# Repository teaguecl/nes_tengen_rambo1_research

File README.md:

# Tengen RAMBO-1 (337006, iNES mapper 64): reverse engineering

A measured description of the Tengen RAMBO-1 mapper chip. It was characterised on a jig (Arduino Mega, later an RP2350
adapter with a PIO engine at 150 MHz), with a logic analyser on a running console, and checked with test ROMs on a real NES.
Every claim in the documents carries an evidence marker.

**Audience:** Software emulator authors, FPGA and cartridge designers.

## Where to start

| If you want to | Read |
|---|---|
| Check a claim | [`docs/findings.md`](docs/findings.md): F-001 to F-090, each with the experiment behind it. This is the heart of the research and everything else is derived from it. |
| Write or fix a mapper 64 emulator | [`docs/emulator_guide.md`](docs/emulator_guide.md). Section 4A is for people who already have an MMC3. For hardware-verified test ROMs, see [`rom/README.md`](rom/README.md) |
| Pins, timing figures and an HDL starting point | [`docs/fpga_notes.md`](docs/fpga_notes.md) |
| Understand how it works | [`docs/functional_description.md`](docs/functional_description.md) |
| Rebuild it in an FPGA or design a cartridge | [`docs/fpga_notes.md`](docs/fpga_notes.md), [`docs/timing_measurements.md`](docs/timing_measurements.md) |
| See what differs from NESdev Wiki | [`docs/nesdev_verification.md`](docs/nesdev_verification.md) |

## What is in the repository

| Path | Contents |
|---|---|
| `docs/` | The documents above, pin maps (`j2_*.csv`), the cart netlist, the logic-analyser guide, the RP2350 adapter plan and bring-up notes |
| `reference/` | `rambo1.py`, a small executable model of the chip (about 200 lines, every rule commented with its finding number), and its unit tests (`test_rambo1.py`) |
| `rom/` | Six test ROMs (G1 to G6, 62 tests) in ca65 assembly. They print PASS or FAIL and run on a real NES. `rom/tools/hwsim.py` runs them on a software model of the chip, and `rom/tools/run_checks.sh` runs everything |
| `firmware/rambo_jig/` | Arduino Mega 2560 firmware for the first jig |
| `firmware/rp2350_jig/` | RP2350 adapter firmware (PIO engine) and the host tools for experiments E2 to E10 |
| `hardware/` | KiCad projects, gerbers and BOMs for the jig board and the two adapters, with a README and the netlist generator |
| `tools/`, `experiments/` | Analysis scripts and experiment definitions for the Mega jig and the logic-analyser captures |
| `captures/`, `results/` | The raw evidence: sigrok captures and CSV logs |
| `pin_check/` | The continuity check of the pinout |

## Headline results

- The chip decodes registers on CPU A0, A13 and A14 only. It has R8, R9 and RF, a 1 KB CHR mode (K), and a CPU-cycle IRQ mode that the MMC3 does not have.
- The power-on state is defined: /IRQ asserted, PRG banks `$1F`, CHR bank 0 in 1 KB mode, latch `$FF`, vertical mirroring, and the counter already running in CPU-cycle mode (F-088).
- The A12 filter needs 16 consecutive M2 falls with A12 low. It samples A12 at the M2 fall only (F-081, F-084).
- The write window closes at the first of the M2 fall, the /ROMSEL rise and the R/W rise, and the data is latched at that instant (F-082).
- CHR bank registers and `$A000` are transparent during the window. R6, R7 and RF are not (F-089).
- The IRQ enable flag is tested at the M2 fall (F-071, F-072, F-074, F-090).
- An A12 to CPU mode switch while the filter is not full expires 4 cycles early (F-087). Test ROM G4 test 13 confirms it on the console.

## The hardware

<table>
<tr>
<td align="center"><br><sub>The three boards: Arduino Mega with its adapter (left), RP2350 adapter (top right) and the RAMBO-1 jig / flash cart (bottom).</sub></td>
<td align="center"><br><sub>The RP2350 adapter connected to the jig board by the 40-way ribbon (J2).</sub></td>
</tr>
<tr>
<td align="center"><br><sub>The jig board with two flash chips, used as a flash cart in an NES: the test ROMs ran from here.</sub></td>
<td align="center"><br><sub>The same cart with the 8-channel logic analyser listening on the J2 header.</sub></td>
</tr>
</table>

## Status and limits

- Everything was measured on **one chip** in one NTSC console. Differences between chip revisions or PAL consoles are unknown.
- Unresolved: the origin of the power-on /IRQ (F-034), the open-drain release time (F-080), the CIC, and pin 19's purpose beyond what F-046 and F-047 show.
- All six test ROMs pass on the real cart (62 tests).

## Building and running

All commands run in a Docker container through `./drun.sh`.
The first call builds the image: cc65 2.19, Python 3, sigrok-cli, SKiDL, CMake, the Pico SDK 2.3.1 and the Arm toolchain.

`./drun.sh --device /dev/ttyACM0 ...` passes the RP2350 adapter's serial port through.

The image does not include KiCad or the Arduino IDE.
Without Docker, install the same tools yourself (see the `Dockerfile`) and drop the `./drun.sh`.

- **Test ROMs:** `./drun.sh "cd rom && make"`

The ready-made images are in `rom/build/` (the six `g*.nes` files).
  Expected MD5 of the six test ROMs (`rom/build/g*.nes`, 524,304 bytes each):

  | Image | Tests | MD5 |
  |---|---|---|
  | `g1_power_on.nes` | Power-on state (after a power cycle only) | `1a89a4dbddda0af36ee58ceca1df30f4` |
  | `g2_banking.nes` | PRG/CHR banking, K/P/C bits, R8/R9, mirroring | `760dfb3409ce149c3a1709a5ff7fed32` |
  | `g3_bus.nes` | Register decode, /CE, bus conflicts, reads | `fb8c870fffdd3aa76c1b4d2a9c10f47f` |
  | `g4_cpu_irq.nes` | CPU-cycle IRQ mode and its timing races | `789a5981e2c5eeb491ff50dc27364bac` |
  | `g5_a12_irq.nes` | A12 (scanline) IRQ, filter, reload | `eef868d8110ecdc8c84e1b7ffd0370ba` |
  | `g6_raster.nes` | IRQ in real rendering, raster splits | `43c3a9863ed705edf7af60c8efafefa6` |

  Check with `./drun.sh "cd rom && md5sum build/g*.nes"`. A different cc65 version could change the bytes; the sums above were made with ca65 V2.18 - Ubuntu 2.19-1, which is what the image installs.
- **Checks without hardware:** `./drun.sh rom/tools/run_checks.sh`

builds the ROMs and runs them on the software models of the chip (the hardware model and the reference model).
- **Reference model:** `./drun.sh python3 -I reference/test_rambo1.py`.
- **RP2350 firmware:** `./drun.sh "cmake -S firmware/rp2350_jig -B firmware/rp2350_jig/build -G Ninja && cmake --build firmware/rp2350_jig/build"` gives `firmware/rp2350_jig/build/rp2350_jig.uf2`. (The container uses Ubuntu's Arm toolchain, so the bytes differ from the author's build.)
- **Netlist generator:** `./drun.sh "cd hardware/generators && python3 rambo1_cart.py"` (SKiDL warns about missing KiCad libraries).
- **Mega firmware:** open `firmware/rambo_jig/rambo_jig.ino` in the Arduino IDE.
- **Before connecting any jig or adapter to a cart, read the safety rules in [`hardware/README.md`](hardware/README.md#safety-read-before-building-the-jig).**

## Credits and licence

Chip identification and the register overview started from the NESdev wiki (mapper 64); Tengen's RAMBO-1 is a trademark of its owners.
The ONE emulator project provided cross-checks.
Licence: code, firmware and test ROM sources are MIT (`LICENSE`). Documents, measurements and captures are CC BY 4.0 (`LICENSE-docs.md`). Board designs are CERN-OHL-P-2.0 (`hardware/LICENSE-hardware.md`).

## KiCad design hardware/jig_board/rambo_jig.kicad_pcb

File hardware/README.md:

# Hardware: jig and adapter boards

KiCad projects for the boards used to characterise the RAMBO-1.

| Folder | Board | Used for |
|---|---|---|
| `jig_board/` | Cart / jig board: the RAMBO-1 (U1) with the NES edge connector footprint, flash chips U2/U3, switches SW1A-C, header J2 and the CIC header J3 | The device under test. In the console it is a flash cart. On the bench it is driven through J2 |
| `mega_adapter/` | Arduino Mega 2560 shield with the 40-way ribbon to J2 | The first jig (`../firmware/rambo_jig/` firmware) |
| `rp2350_adapter/` | Olimex RP2350-PICO2-BB48 carrier with three 74HCT541 drivers (5 V stimulus) and two 74LVC541A buffers (outputs) | The PIO-engine adapter (`../firmware/rp2350_jig/` firmware), experiments E2 to E10 |
| `generators/` | `rambo1_cart.py` (SKiDL netlist of the cart from the verified continuity map), `rambo1_cart_sklib.py`, footprint generators, adapter pin maps | Regenerate the netlist and footprints |

Each board folder has the KiCad project (`.kicad_pro`, `.kicad_sch`, `.kicad_pcb`), its symbol library, the `nes_cart.pretty` footprints.

## Status

- The designs were built and used. The RP2350 adapter board was checked against the pin map (all 33 signals match) and is documented in
  [`../docs/rp2350_adapter_plan.md`](../docs/rp2350_adapter_plan.md) and [`../docs/rp2350_bringup.md`](../docs/rp2350_bringup.md).
- Loopback calibration of the adapter's edge timing has not been done (it needs jumper wires). Treat adapter timings of a few ns as uncertain.
- The Olimex module is third-party: https://github.com/OLIMEX/RP2350-PICO2-BB48 (design files and documents).
- Open the projects with KiCad 10. Library tables use `${KIPRJMOD}`, so they should open from any location.

## Safety (read before building the jig)

- Never connect a jig or adapter while the cart is in a console.
- Remove flash chips U2 and U3 in jig mode, so nothing else drives the CPU data bus.
- Fit SW1C (RAMBO pin 19 to GND). Switch SW1A and SW1B off (flash write enable).
- Enable cart power before the drivers, and disable the drivers before cutting power.
- Never connect the Mega jig, the RP2350 adapter and the logic analyser to the cart at the same time. Power the console off before moving analyser leads.
- Use a powered USB hub for long adapter runs. Two unpowered runs crashed the host's USB controller.

The full rules are in [`../CLAUDE.md`](../CLAUDE.md) and [`../docs/hardware.md`](../docs/hardware.md).

Licence: CERN-OHL-P-2.0, see `LICENSE-hardware.md`.

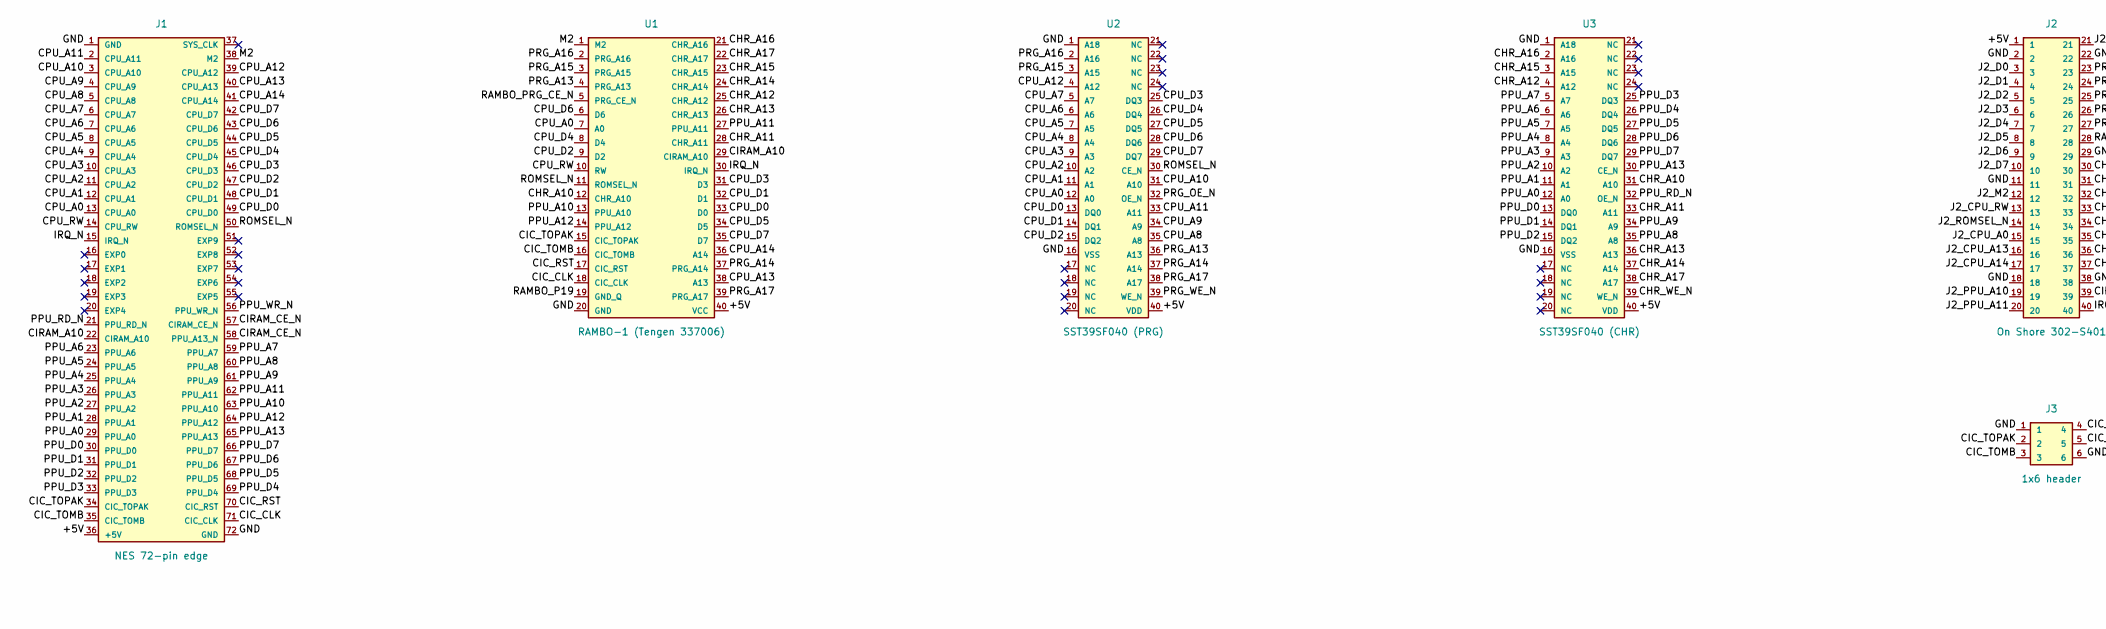
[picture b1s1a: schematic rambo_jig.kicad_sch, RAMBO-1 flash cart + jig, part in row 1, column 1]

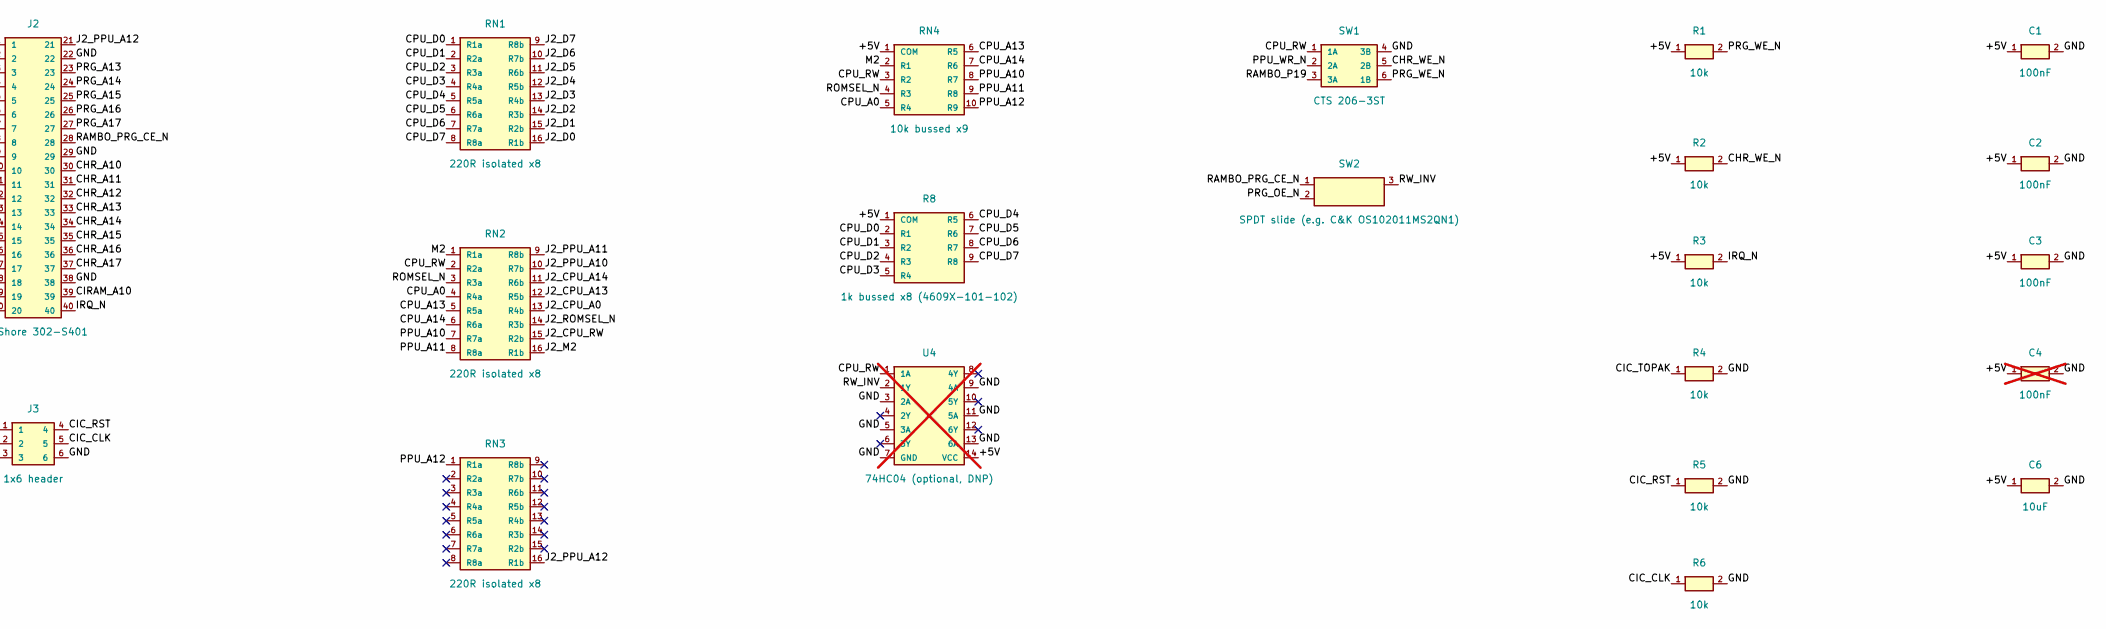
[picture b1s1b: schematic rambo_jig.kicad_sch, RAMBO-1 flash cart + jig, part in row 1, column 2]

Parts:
C1, C2, C3: 100nF; C_Disc_D5.0mm_W2.5mm_P5.00mm
C4: 100nF; C_Disc_D5.0mm_W2.5mm_P5.00mm; not fitted
C6: 10uF; CP_Radial_D5.0mm_P2.00mm
J1: NES 72-pin edge; NES_Edge_72_P2.50mm
J2: On Shore 302-S401; IDC-Header_2x20_P2.54mm_Vertical
J3: 1x6 header; PinHeader_1x06_P2.54mm_Vertical
R1, R2, R3, R4, R5, R6: 10k; R_Axial_DIN0207_L6.3mm_D2.5mm_P10.16mm_Horizontal
R8: 1k bussed x8 (4609X-101-102); R_Array_SIP9
RN1, RN2, RN3: 220R isolated x8; DIP-16_W7.62mm
RN4: 10k bussed x9; R_Array_SIP10
SW1: CTS 206-3ST; SW_DIP_SPSTx03_Slide_9.78x9.8mm_W7.62mm_P2.54mm
SW2: SPDT slide (e.g. C&K OS102011MS2QN1); SPDT_OS102011_CNK
U1: RAMBO-1 (Tengen 337006); HWS7264_ZIF40
U2: SST39SF040 (PRG); HWS7264_ZIF40_Flash32
U3: SST39SF040 (CHR); HWS7264_ZIF40_Flash32
U4: 74HC04 (optional, DNP); DIP-14_W7.62mm; not fitted

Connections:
/+5V: C1.1, C2.1, C3.1, C4.1, C6.1, J1.36 (+5V), J2.1, R1.1, R2.1, R3.1, R8.1 (COM), RN4.1 (COM), U1.40 (VCC), U2.40 (VDD), U3.40 (VDD), U4.14 (VCC)
/CHR_A10: J2.30, U1.12 (CHR_A10), U3.31 (A10)
/CHR_A11: J2.31, U1.28 (CHR_A11), U3.33 (A11)
/CHR_A12: J2.32, U1.25 (CHR_A12), U3.4 (A12)
/CHR_A13: J2.33, U1.26 (CHR_A13), U3.36 (A13)
/CHR_A14: J2.34, U1.24 (CHR_A14), U3.37 (A14)
/CHR_A15: J2.35, U1.23 (CHR_A15), U3.3 (A15)
/CHR_A16: J2.36, U1.21 (CHR_A16), U3.2 (A16)
/CHR_A17: J2.37, U1.22 (CHR_A17), U3.38 (A17)
/CHR_WE_N: R2.2, SW1.5 (2B), U3.39 (WE_N)
/CIC_CLK: J1.71 (CIC_CLK), J3.5, R6.1, U1.18 (CIC_CLK)
/CIC_RST: J1.70 (CIC_RST), J3.4, R5.1, U1.17 (CIC_RST)
/CIC_TOMB: J1.35 (CIC_TOMB), J3.3, U1.16 (CIC_TOMB)
/CIC_TOPAK: J1.34 (CIC_TOPAK), J3.2, R4.1, U1.15 (CIC_TOPAK)
/CIRAM_A10: J1.22 (CIRAM_A10), J2.39, U1.29 (CIRAM_A10)
/CIRAM_CE_N: J1.57 (CIRAM_CE_N), J1.58 (PPU_A13_N)
/CPU_A0: J1.13 (CPU_A0), RN2.4 (R4a), RN4.5 (R4), U1.7 (A0), U2.12 (A0)
/CPU_A1: J1.12 (CPU_A1), U2.11 (A1)
/CPU_A2: J1.11 (CPU_A2), U2.10 (A2)
/CPU_A3: J1.10 (CPU_A3), U2.9 (A3)
/CPU_A4: J1.9 (CPU_A4), U2.8 (A4)
/CPU_A5: J1.8 (CPU_A5), U2.7 (A5)
/CPU_A6: J1.7 (CPU_A6), U2.6 (A6)
/CPU_A7: J1.6 (CPU_A7), U2.5 (A7)
/CPU_A8: J1.5 (CPU_A8), U2.35 (A8)
/CPU_A9: J1.4 (CPU_A9), U2.34 (A9)
/CPU_A10: J1.3 (CPU_A10), U2.31 (A10)
/CPU_A11: J1.2 (CPU_A11), U2.33 (A11)
/CPU_A12: J1.39 (CPU_A12), U2.4 (A12)
/CPU_A13: J1.40 (CPU_A13), RN2.5 (R5a), RN4.6 (R5), U1.38 (A13)
/CPU_A14: J1.41 (CPU_A14), RN2.6 (R6a), RN4.7 (R6), U1.36 (A14)
/CPU_D0: J1.49 (CPU_D0), R8.2 (R1), RN1.1 (R1a), U1.33 (D0), U2.13 (DQ0)
/CPU_D1: J1.48 (CPU_D1), R8.3 (R2), RN1.2 (R2a), U1.32 (D1), U2.14 (DQ1)
/CPU_D2: J1.47 (CPU_D2), R8.4 (R3), RN1.3 (R3a), U1.9 (D2), U2.15 (DQ2)
/CPU_D3: J1.46 (CPU_D3), R8.5 (R4), RN1.4 (R4a), U1.31 (D3), U2.25 (DQ3)
/CPU_D4: J1.45 (CPU_D4), R8.6 (R5), RN1.5 (R5a), U1.8 (D4), U2.26 (DQ4)
/CPU_D5: J1.44 (CPU_D5), R8.7 (R6), RN1.6 (R6a), U1.34 (D5), U2.27 (DQ5)
/CPU_D6: J1.43 (CPU_D6), R8.8 (R7), RN1.7 (R7a), U1.6 (D6), U2.28 (DQ6)
/CPU_D7: J1.42 (CPU_D7), R8.9 (R8), RN1.8 (R8a), U1.35 (D7), U2.29 (DQ7)
/CPU_RW: J1.14 (CPU_RW), RN2.2 (R2a), RN4.3 (R2), SW1.1 (1A), U1.10 (RW), U4.1 (1A)
/GND: C1.2, C2.2, C3.2, C4.2, C6.2, J1.1 (GND), J1.72 (GND), J2.2, J2.11, J2.18, J2.22, J2.29, J2.38, J3.1, J3.6, R4.2, R5.2, R6.2, SW1.4 (3B), U1.20 (GND), U2.1 (A18), U2.16 (VSS), U3.1 (A18), U3.16 (VSS), U4.3 (2A), U4.5 (3A), U4.7 (GND), U4.9 (4A), U4.11 (5A), U4.13 (6A)
/IRQ_N: J1.15 (IRQ_N), J2.40, R3.2, U1.30 (IRQ_N)
/J2_CPU_A0: J2.15, RN2.13 (R4b)
/J2_CPU_A13: J2.16, RN2.12 (R5b)
/J2_CPU_A14: J2.17, RN2.11 (R6b)
/J2_CPU_RW: J2.13, RN2.15 (R2b)
/J2_D0: J2.3, RN1.16 (R1b)
/J2_D1: J2.4, RN1.15 (R2b)
/J2_D2: J2.5, RN1.14 (R3b)
/J2_D3: J2.6, RN1.13 (R4b)
/J2_D4: J2.7, RN1.12 (R5b)
/J2_D5: J2.8, RN1.11 (R6b)
/J2_D6: J2.9, RN1.10 (R7b)
/J2_D7: J2.10, RN1.9 (R8b)
/J2_M2: J2.12, RN2.16 (R1b)
/J2_PPU_A10: J2.19, RN2.10 (R7b)
/J2_PPU_A11: J2.20, RN2.9 (R8b)
/J2_PPU_A12: J2.21, RN3.16 (R1b)
/J2_ROMSEL_N: J2.14, RN2.14 (R3b)
/M2: J1.38 (M2), RN2.1 (R1a), RN4.2 (R1), U1.1 (M2)
/PPU_A0: J1.29 (PPU_A0), U3.12 (A0)
/PPU_A1: J1.28 (PPU_A1), U3.11 (A1)
/PPU_A2: J1.27 (PPU_A2), U3.10 (A2)
/PPU_A3: J1.26 (PPU_A3), U3.9 (A3)
/PPU_A4: J1.25 (PPU_A4), U3.8 (A4)
/PPU_A5: J1.24 (PPU_A5), U3.7 (A5)
/PPU_A6: J1.23 (PPU_A6), U3.6 (A6)
/PPU_A7: J1.59 (PPU_A7), U3.5 (A7)
/PPU_A8: J1.60 (PPU_A8), U3.35 (A8)
/PPU_A9: J1.61 (PPU_A9), U3.34 (A9)
/PPU_A10: J1.63 (PPU_A10), RN2.7 (R7a), RN4.8 (R7), U1.13 (PPU_A10)
/PPU_A11: J1.62 (PPU_A11), RN2.8 (R8a), RN4.9 (R8), U1.27 (PPU_A11)
/PPU_A12: J1.64 (PPU_A12), RN3.1 (R1a), RN4.10 (R9), U1.14 (PPU_A12)
/PPU_A13: J1.65 (PPU_A13), U3.30 (CE_N)
/PPU_D0: J1.30 (PPU_D0), U3.13 (DQ0)
/PPU_D1: J1.31 (PPU_D1), U3.14 (DQ1)
/PPU_D2: J1.32 (PPU_D2), U3.15 (DQ2)
/PPU_D3: J1.33 (PPU_D3), U3.25 (DQ3)
/PPU_D4: J1.69 (PPU_D4), U3.26 (DQ4)
/PPU_D5: J1.68 (PPU_D5), U3.27 (DQ5)
/PPU_D6: J1.67 (PPU_D6), U3.28 (DQ6)
/PPU_D7: J1.66 (PPU_D7), U3.29 (DQ7)
/PPU_RD_N: J1.21 (PPU_RD_N), U3.32 (OE_N)
/PPU_WR_N: J1.56 (PPU_WR_N), SW1.2 (2A)
/PRG_A13: J2.23, U1.4 (PRG_A13), U2.36 (A13)
/PRG_A14: J2.24, U1.37 (PRG_A14), U2.37 (A14)
/PRG_A15: J2.25, U1.3 (PRG_A15), U2.3 (A15)
/PRG_A16: J2.26, U1.2 (PRG_A16), U2.2 (A16)
/PRG_A17: J2.27, U1.39 (PRG_A17), U2.38 (A17)
/PRG_OE_N: SW2.2, U2.32 (OE_N)
/PRG_WE_N: R1.2, SW1.6 (1B), U2.39 (WE_N)
/RAMBO_P19: SW1.3 (3A), U1.19 (GND_Q)
/RAMBO_PRG_CE_N: J2.28, SW2.1, U1.5 (PRG_CE_N)
/ROMSEL_N: J1.50 (ROMSEL_N), RN2.3 (R3a), RN4.4 (R3), U1.11 (ROMSEL_N), U2.30 (CE_N)
/RW_INV: SW2.3, U4.2 (1Y)

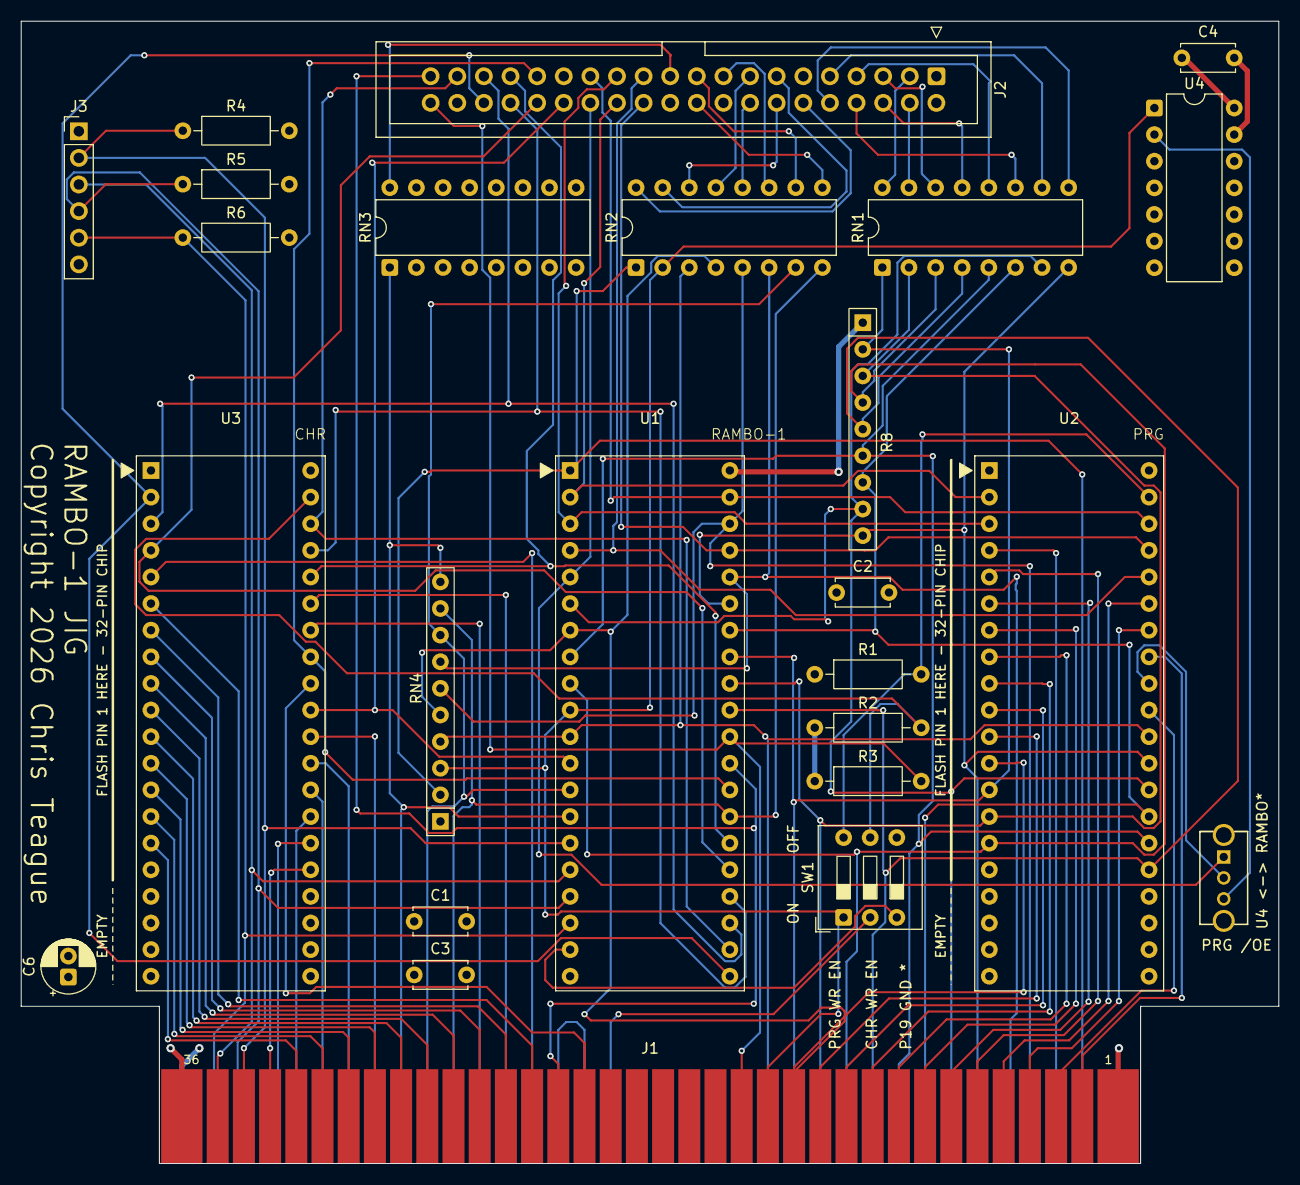
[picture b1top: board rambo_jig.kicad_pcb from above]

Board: 4 copper layers, 120.0 x 109.0 mm, 25 parts (0 on the bottom side), 95 nets.

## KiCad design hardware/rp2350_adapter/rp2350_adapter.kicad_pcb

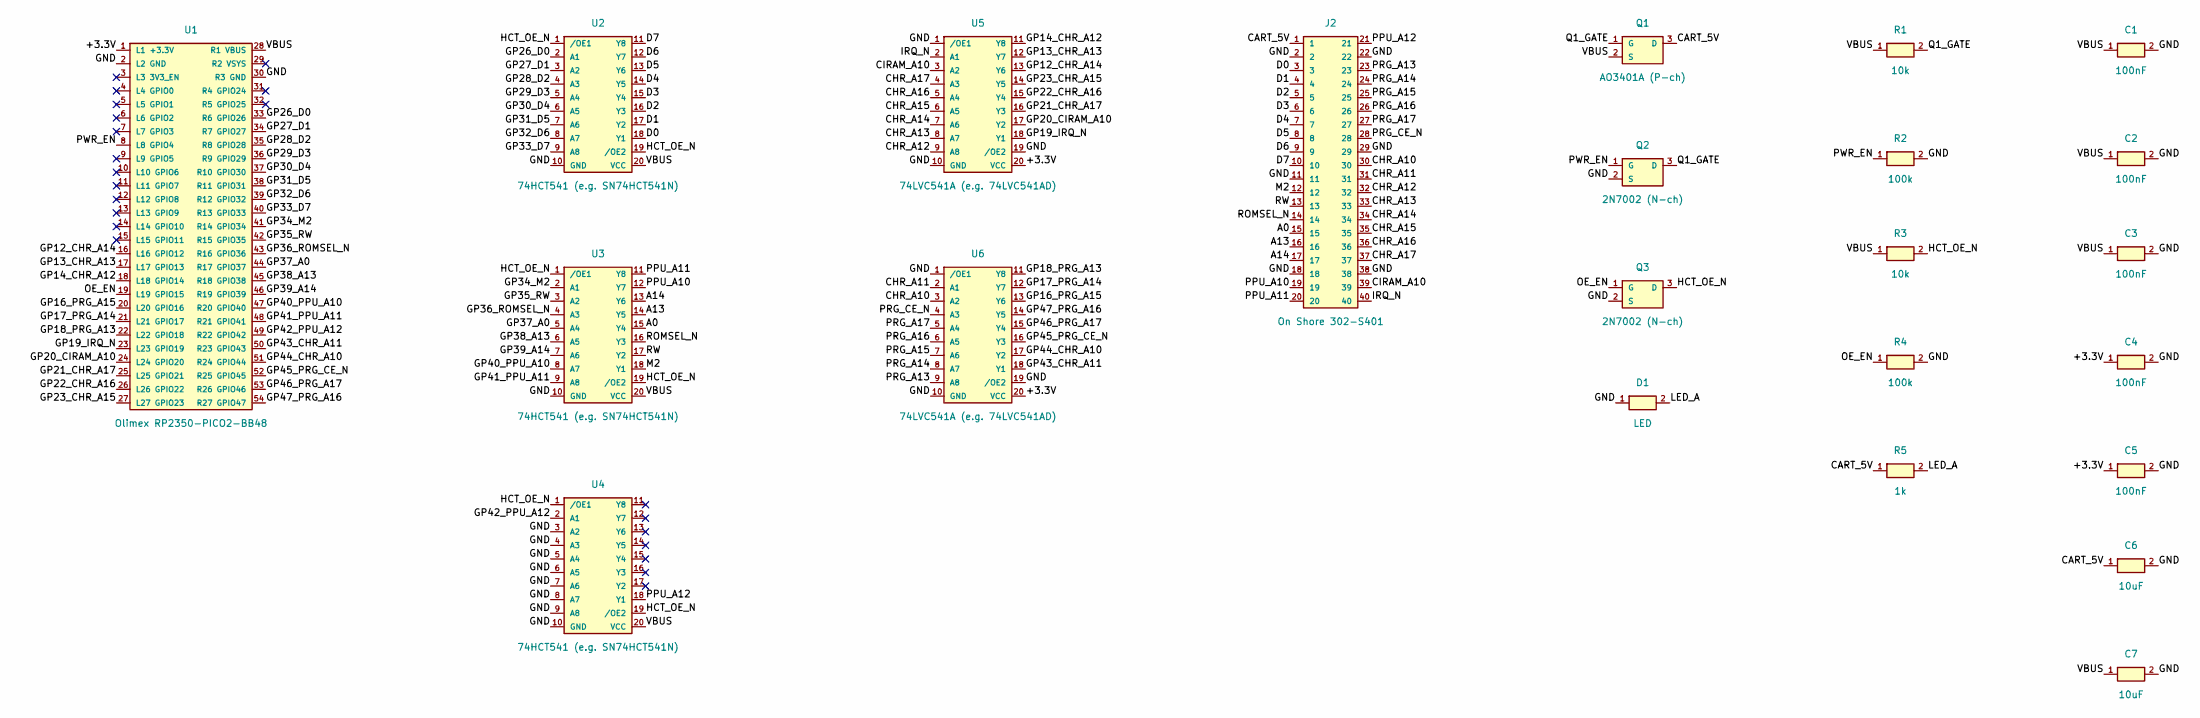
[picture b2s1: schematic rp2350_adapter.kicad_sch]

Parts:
C1, C2, C3, C4, C5: 100nF; C_Disc_D5.0mm_W2.5mm_P5.00mm
C6, C7: 10uF; CP_Radial_D5.0mm_P2.00mm
D1: LED; LED_D3.0mm
J2: On Shore 302-S401; IDC-Header_2x20_P2.54mm_Vertical
Q1: AO3401A (P-ch); SOT-23
Q2, Q3: 2N7002 (N-ch); SOT-23
R1, R3: 10k; R_Axial_DIN0207_L6.3mm_D2.5mm_P10.16mm_Horizontal
R2, R4: 100k; R_Axial_DIN0207_L6.3mm_D2.5mm_P10.16mm_Horizontal
R5: 1k; R_Axial_DIN0207_L6.3mm_D2.5mm_P10.16mm_Horizontal
U1: Olimex RP2350-PICO2-BB48; Olimex_BB48_Socket
U2, U3, U4: 74HCT541 (e.g. SN74HCT541N); DIP-20_W7.62mm
U5, U6: 74LVC541A (e.g. 74LVC541AD); SOIC-20W_7.5x12.8mm_P1.27mm

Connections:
/+3.3V: C4.1, C5.1, U1.1 (L1_+3.3V), U5.20 (VCC), U6.20 (VCC)
/A0: J2.15, U3.15 (Y4)
/A13: J2.16, U3.14 (Y5)
/A14: J2.17, U3.13 (Y6)
/CART_5V: C6.1, J2.1, Q1.3 (D), R5.1
/CHR_A10: J2.30, U6.3 (A2)
/CHR_A11: J2.31, U6.2 (A1)
/CHR_A12: J2.32, U5.9 (A8)
/CHR_A13: J2.33, U5.8 (A7)
/CHR_A14: J2.34, U5.7 (A6)
/CHR_A15: J2.35, U5.6 (A5)
/CHR_A16: J2.36, U5.5 (A4)
/CHR_A17: J2.37, U5.4 (A3)
/CIRAM_A10: J2.39, U5.3 (A2)
/D0: J2.3, U2.18 (Y1)
/D1: J2.4, U2.17 (Y2)
/D2: J2.5, U2.16 (Y3)
/D3: J2.6, U2.15 (Y4)
/D4: J2.7, U2.14 (Y5)
/D5: J2.8, U2.13 (Y6)
/D6: J2.9, U2.12 (Y7)
/D7: J2.10, U2.11 (Y8)
/GND: C1.2, C2.2, C3.2, C4.2, C5.2, C6.2, C7.2, D1.1, J2.2, J2.11, J2.18, J2.22, J2.29, J2.38, Q2.2 (S), Q3.2 (S), R2.2, R4.2, U1.2 (L2_GND), U1.30 (R3_GND), U2.10 (GND), U3.10 (GND), U4.3 (A2), U4.4 (A3), U4.5 (A4), U4.6 (A5), U4.7 (A6), U4.8 (A7), U4.9 (A8), U4.10 (GND), U5.1 (/OE1), U5.10 (GND), U5.19 (/OE2), U6.1 (/OE1), U6.10 (GND), U6.19 (/OE2)
/GP12_CHR_A14: U1.16 (L16_GPIO12), U5.13 (Y6)
/GP13_CHR_A13: U1.17 (L17_GPIO13), U5.12 (Y7)
/GP14_CHR_A12: U1.18 (L18_GPIO14), U5.11 (Y8)
/GP16_PRG_A15: U1.20 (L20_GPIO16), U6.13 (Y6)
/GP17_PRG_A14: U1.21 (L21_GPIO17), U6.12 (Y7)
/GP18_PRG_A13: U1.22 (L22_GPIO18), U6.11 (Y8)
/GP19_IRQ_N: U1.23 (L23_GPIO19), U5.18 (Y1)
/GP20_CIRAM_A10: U1.24 (L24_GPIO20), U5.17 (Y2)
/GP21_CHR_A17: U1.25 (L25_GPIO21), U5.16 (Y3)
/GP22_CHR_A16: U1.26 (L26_GPIO22), U5.15 (Y4)
/GP23_CHR_A15: U1.27 (L27_GPIO23), U5.14 (Y5)
/GP26_D0: U1.33 (R6_GPIO26), U2.2 (A1)
/GP27_D1: U1.34 (R7_GPIO27), U2.3 (A2)
/GP28_D2: U1.35 (R8_GPIO28), U2.4 (A3)
/GP29_D3: U1.36 (R9_GPIO29), U2.5 (A4)
/GP30_D4: U1.37 (R10_GPIO30), U2.6 (A5)
/GP31_D5: U1.38 (R11_GPIO31), U2.7 (A6)
/GP32_D6: U1.39 (R12_GPIO32), U2.8 (A7)
/GP33_D7: U1.40 (R13_GPIO33), U2.9 (A8)
/GP34_M2: U1.41 (R14_GPIO34), U3.2 (A1)
/GP35_RW: U1.42 (R15_GPIO35), U3.3 (A2)
/GP36_ROMSEL_N: U1.43 (R16_GPIO36), U3.4 (A3)
/GP37_A0: U1.44 (R17_GPIO37), U3.5 (A4)
/GP38_A13: U1.45 (R18_GPIO38), U3.6 (A5)
/GP39_A14: U1.46 (R19_GPIO39), U3.7 (A6)
/GP40_PPU_A10: U1.47 (R20_GPIO40), U3.8 (A7)
/GP41_PPU_A11: U1.48 (R21_GPIO41), U3.9 (A8)
/GP42_PPU_A12: U1.49 (R22_GPIO42), U4.2 (A1)
/GP43_CHR_A11: U1.50 (R23_GPIO43), U6.18 (Y1)
/GP44_CHR_A10: U1.51 (R24_GPIO44), U6.17 (Y2)
/GP45_PRG_CE_N: U1.52 (R25_GPIO45), U6.16 (Y3)
/GP46_PRG_A17: U1.53 (R26_GPIO46), U6.15 (Y4)
/GP47_PRG_A16: U1.54 (R27_GPIO47), U6.14 (Y5)
/HCT_OE_N: Q3.3 (D), R3.2, U2.1 (/OE1), U2.19 (/OE2), U3.1 (/OE1), U3.19 (/OE2), U4.1 (/OE1), U4.19 (/OE2)
/IRQ_N: J2.40, U5.2 (A1)
/LED_A: D1.2, R5.2
/M2: J2.12, U3.18 (Y1)
/OE_EN: Q3.1 (G), R4.1, U1.19 (L19_GPIO15)
/PPU_A10: J2.19, U3.12 (Y7)
/PPU_A11: J2.20, U3.11 (Y8)
/PPU_A12: J2.21, U4.18 (Y1)
/PRG_A13: J2.23, U6.9 (A8)
/PRG_A14: J2.24, U6.8 (A7)
/PRG_A15: J2.25, U6.7 (A6)
/PRG_A16: J2.26, U6.6 (A5)
/PRG_A17: J2.27, U6.5 (A4)
/PRG_CE_N: J2.28, U6.4 (A3)
/PWR_EN: Q2.1 (G), R2.1, U1.8 (L8_GPIO4)
/Q1_GATE: Q1.1 (G), Q2.3 (D), R1.2
/ROMSEL_N: J2.14, U3.16 (Y3)
/RW: J2.13, U3.17 (Y2)
/VBUS: C1.1, C2.1, C3.1, C7.1, Q1.2 (S), R1.1, R3.1, U1.28 (R1_VBUS), U2.20 (VCC), U3.20 (VCC), U4.20 (VCC)

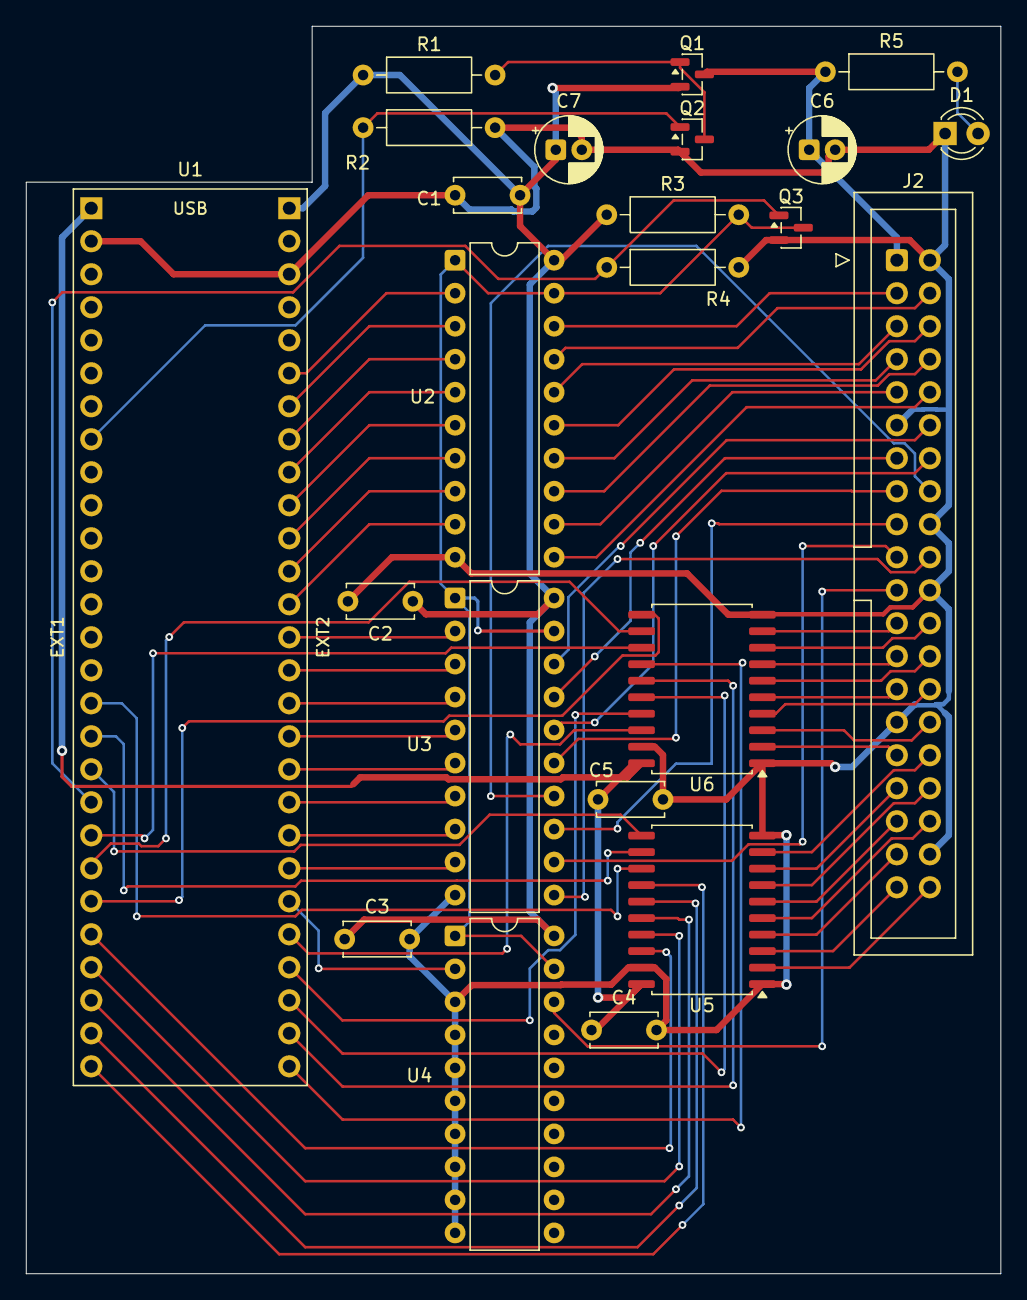
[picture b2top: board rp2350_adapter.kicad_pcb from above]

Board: 2 copper layers, 75.0 x 96.0 mm, 23 parts (0 on the bottom side), 75 nets.

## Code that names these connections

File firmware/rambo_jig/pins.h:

// pins.h: the only place that knows how signals map to AVR port bits.
// Source: docs/j2_mega_pinmap.csv (Mega adapter). Do not hard-code bits elsewhere.
#pragma once
#include <Arduino.h>

// ---- Mega -> RAMBO (outputs) ----------------------------------------------
// CPU data bus D0-D7: PORTA, bit n = Dn (D22-D29).
#define DATA_PORT   PORTA
#define DATA_DDR    DDRA

// Control/address bits on PORTC (D30-D37). Bit order is routing order, not signal order.
#define CTRL_PORT   PORTC
#define CTRL_DDR    DDRC
#define BIT_M2        7   // D30
#define BIT_RW        6   // D31
#define BIT_ROMSEL_N  5   // D32
#define BIT_A0        4   // D33
#define BIT_A13       3   // D34
#define BIT_A14       2   // D35
#define BIT_PPU_A10   1   // D36
#define BIT_PPU_A11   0   // D37

#define M2_MASK        _BV(BIT_M2)
#define RW_MASK        _BV(BIT_RW)
#define ROMSEL_N_MASK  _BV(BIT_ROMSEL_N)
#define CPU_ADDR_MASK  (_BV(BIT_A0) | _BV(BIT_A13) | _BV(BIT_A14))
#define PPU_ADDR_MASK  (_BV(BIT_PPU_A10) | _BV(BIT_PPU_A11))

// PPU A12 on PD7 (D38). PD0 (D21, INT0) is /IRQ and must stay an input.
#define PPU_A12_PORT  PORTD
#define PPU_A12_DDR   DDRD
#define BIT_PPU_A12   7
#define PPU_A12_MASK  _BV(BIT_PPU_A12)

// Convert a CPU address ($8000-$FFFF) to the A0/A13/A14 bits on CTRL_PORT.
// A15 is implied by /ROMSEL low; A1-A12 are not wired to the RAMBO.
static inline uint8_t cpuAddrToCtrl(uint16_t addr) {
  uint8_t v = 0;
  if (addr & 0x0001) v |= _BV(BIT_A0);
  if (addr & 0x2000) v |= _BV(BIT_A13);
  if (addr & 0x4000) v |= _BV(BIT_A14);
  return v;
}

// ---- RAMBO pin 19 (flying lead) --------------------------------------------
// Mega D2 = PE4 -> 1 kohm -> RAMBO pin 19 net (SW1 contact 3A). SW1C must be OFF while this is used.
// Pin 19 is an input-style pad that the original board ties to GND (docs/findings.md F-043).
// Idle state is released (input, no pull-up) so it comes up undriven at reset.
#define P19_PORT   PORTE
#define P19_DDR    DDRE
#define P19_PIN    PINE
#define BIT_P19    4
#define P19_MASK   _BV(BIT_P19)

// mode: 0 = drive low, 1 = drive high, other = release (high impedance).
static inline void setPin19(uint8_t mode) {
  if (mode == 0)      { P19_PORT &= ~P19_MASK; P19_DDR |= P19_MASK; }
  else if (mode == 1) { P19_PORT |= P19_MASK;  P19_DDR |= P19_MASK; }
  else                { P19_DDR &= ~P19_MASK;  P19_PORT &= ~P19_MASK; }
}
static inline char pin19State() {
  if (!(P19_DDR & P19_MASK)) return 'Z';
  return (P19_PORT & P19_MASK) ? 'H' : 'L';
}

// ---- RAMBO -> Mega (inputs) -----------------------------------------------
// PORTG: PG2=PRG_A13, PG1=PRG_A14, PG0=PRG_A15
// PORTL: PL7=PRG_A16, PL6=PRG_A17, PL5=PRG_CE_N, PL4..PL0=CHR_A10..CHR_A14
// PORTB: PB3=CHR_A15, PB2=CHR_A16, PB1=CHR_A17, PB0=CIRAM_A10
// PORTD: PD0=IRQ_N (INT0, D21)
#define IRQ_PIN        21
#define IRQ_PIN_REG    PIND
#define BIT_IRQ_N      0

// Packed output word, in signal order (independent of port bit order).
enum OutBit : uint8_t {
  OUT_PRG_A13 = 0, OUT_PRG_A14, OUT_PRG_A15, OUT_PRG_A16, OUT_PRG_A17,
  OUT_PRG_CE_N,
  OUT_CHR_A10, OUT_CHR_A11, OUT_CHR_A12, OUT_CHR_A13,
  OUT_CHR_A14, OUT_CHR_A15, OUT_CHR_A16, OUT_CHR_A17,
  OUT_CIRAM_A10,
  OUT_IRQ_N,
  OUT_COUNT
};

static const char *const OUT_NAMES[OUT_COUNT] = {
  "PRG_A13", "PRG_A14", "PRG_A15", "PRG_A16", "PRG_A17",
  "PRG_CE_N",
  "CHR_A10", "CHR_A11", "CHR_A12", "CHR_A13",
  "CHR_A14", "CHR_A15", "CHR_A16", "CHR_A17",
  "CIRAM_A10",
  "IRQ_N"
};

#define PUT(word, port, pbit, sig) \
  do { if ((port) & _BV(pbit)) (word) |= (uint16_t)1 << (sig); } while (0)

// Pack raw port reads (PING, PINL, PINB, IRQ_PIN_REG) into the signal-ordered word.
static inline uint16_t packOutputs(uint8_t g, uint8_t l, uint8_t b, uint8_t d) {
  uint16_t w = 0;
  PUT(w, g, 2, OUT_PRG_A13);
  PUT(w, g, 1, OUT_PRG_A14);
  PUT(w, g, 0, OUT_PRG_A15);
  PUT(w, l, 7, OUT_PRG_A16);
  PUT(w, l, 6, OUT_PRG_A17);
  PUT(w, l, 5, OUT_PRG_CE_N);
  PUT(w, l, 4, OUT_CHR_A10);
  PUT(w, l, 3, OUT_CHR_A11);
  PUT(w, l, 2, OUT_CHR_A12);
  PUT(w, l, 1, OUT_CHR_A13);
  PUT(w, l, 0, OUT_CHR_A14);
  PUT(w, b, 3, OUT_CHR_A15);
  PUT(w, b, 2, OUT_CHR_A16);
  PUT(w, b, 1, OUT_CHR_A17);
  PUT(w, b, 0, OUT_CIRAM_A10);
  PUT(w, d, BIT_IRQ_N, OUT_IRQ_N);
  return w;
}

// Sample all RAMBO outputs. Ports are read back-to-back (not one instant).
static inline uint16_t readOutputs() {
  uint8_t g = PING, l = PINL, b = PINB, d = IRQ_PIN_REG;
  return packOutputs(g, l, b, d);
}

// Define every pin at the start of setup(). PORT is written before DDR so each
// output comes up at its idle level with no glitch.
// Idle: M2 low, R/W high, /ROMSEL high, data high (matches the cart pull-ups).
static inline void initPins() {
  CTRL_PORT = RW_MASK | ROMSEL_N_MASK;   // M2 low, A0/A13/A14/PPU A10/A11 low
  CTRL_DDR  = 0xFF;
  DATA_PORT = 0xFF;
  DATA_DDR  = 0xFF;
  PPU_A12_PORT &= ~PPU_A12_MASK;
  PPU_A12_DDR  |= PPU_A12_MASK;
  DDRG &= ~0x07; PORTG &= ~0x07;         // inputs, no internal pull-ups
  DDRL  = 0x00;  PORTL  = 0x00;
  DDRB &= ~0x0F; PORTB &= ~0x0F;
  DDRD &= ~_BV(BIT_IRQ_N); PORTD &= ~_BV(BIT_IRQ_N);  // cart has the 10k pull-up
  setPin19(2);                           // pin 19 released
}

// ---- Table of every Mega output, for pin-check ---------------------------
struct DrivePin {
  const char *name;
  volatile uint8_t *port;
  volatile uint8_t *pin;
  uint8_t mask;
  bool idleHigh;   // level set by initPins()
};

#define DRIVE_PIN(n, port, pin, bit, idle) { n, &port, &pin, _BV(bit), idle }
static const DrivePin DRIVE_PINS[] = {
  DRIVE_PIN("D0", PORTA, PINA, 0, true), DRIVE_PIN("D1", PORTA, PINA, 1, true),
  DRIVE_PIN("D2", PORTA, PINA, 2, true), DRIVE_PIN("D3", PORTA, PINA, 3, true),
  DRIVE_PIN("D4", PORTA, PINA, 4, true), DRIVE_PIN("D5", PORTA, PINA, 5, true),
  DRIVE_PIN("D6", PORTA, PINA, 6, true), DRIVE_PIN("D7", PORTA, PINA, 7, true),
  DRIVE_PIN("M2",       CTRL_PORT, PINC, BIT_M2,       false),
  DRIVE_PIN("RW",       CTRL_PORT, PINC, BIT_RW,       true),
  DRIVE_PIN("ROMSEL_N", CTRL_PORT, PINC, BIT_ROMSEL_N, true),
  DRIVE_PIN("A0",       CTRL_PORT, PINC, BIT_A0,       false),
  DRIVE_PIN("A13",      CTRL_PORT, PINC, BIT_A13,      false),
  DRIVE_PIN("A14",      CTRL_PORT, PINC, BIT_A14,      false),
  DRIVE_PIN("PPU_A10",  CTRL_PORT, PINC, BIT_PPU_A10,  false),
  DRIVE_PIN("PPU_A11",  CTRL_PORT, PINC, BIT_PPU_A11,  false),
  DRIVE_PIN("PPU_A12",  PPU_A12_PORT, PIND, BIT_PPU_A12, false),
};
#define DRIVE_PIN_COUNT (sizeof(DRIVE_PINS) / sizeof(DRIVE_PINS[0]))

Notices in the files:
hardware/jig_board/rambo_jig.kicad_pcb:
Copyright 2026 Chris Teague
